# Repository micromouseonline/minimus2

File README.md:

# MINIMUS-2
A half size micromouse design.

## Intent

Create hardware and software for a half-size micromouse robot. The design should be simple and easy to reproduce. It is not necessarily meant to compete at the highest levels. Rather, it should provide a working platform for beginners while still forming the basis for more performant derivatives.

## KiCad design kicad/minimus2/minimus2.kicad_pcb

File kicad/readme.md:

# KiCAD design files for Minimus

All ECAD work is done wih KiCad V8.0

## Libraries

 - Add the JLCPCB parts library by following the instructions here:
    https://github.com/CDFER/JLCPCB-Kicad-Library

    This library contains all the basic parts avaiable from the JLCPCB assembly service, inclluding their footprints and part references.

    As far as I know, the library source is updated every day but the local copy is not so all parts should be checked at the time of a request for manufacture.

    Updates can be done manually from the Plugin manager.

    Since the library is a git repository, it might be possible to clone or fork it, create a local branch and edit the footprints that way.

 - There will also be a custom project library for the parts used in minimus.

## Plugins

 - Add the KiCAD JLC PCB Tools by following the instructions here
     https://github.com/Bouni/kicad-jlcpcb-tools

## Schematic Style

Note that the symbols used by the JLCPCB parts library do not match the symbols that are the default in KiCAD supplied libraries. The most important attributes are all those relating specifically to the JLCPCB part - size, part number, type and so on. If the symbols are a problem, it might be best to copy each part from the JLCPCB library to the project library and edit the symbol there.

## PCB Style

For a half-size mouse, all the components are small and contained in a small PCB. It is not practical to have the component reference and value for all parts. If the boards are to be manufacured by a service, this is not a great problem. A reference diagram showing the part placement from the FAB layers would be helpful for testing and debugging.

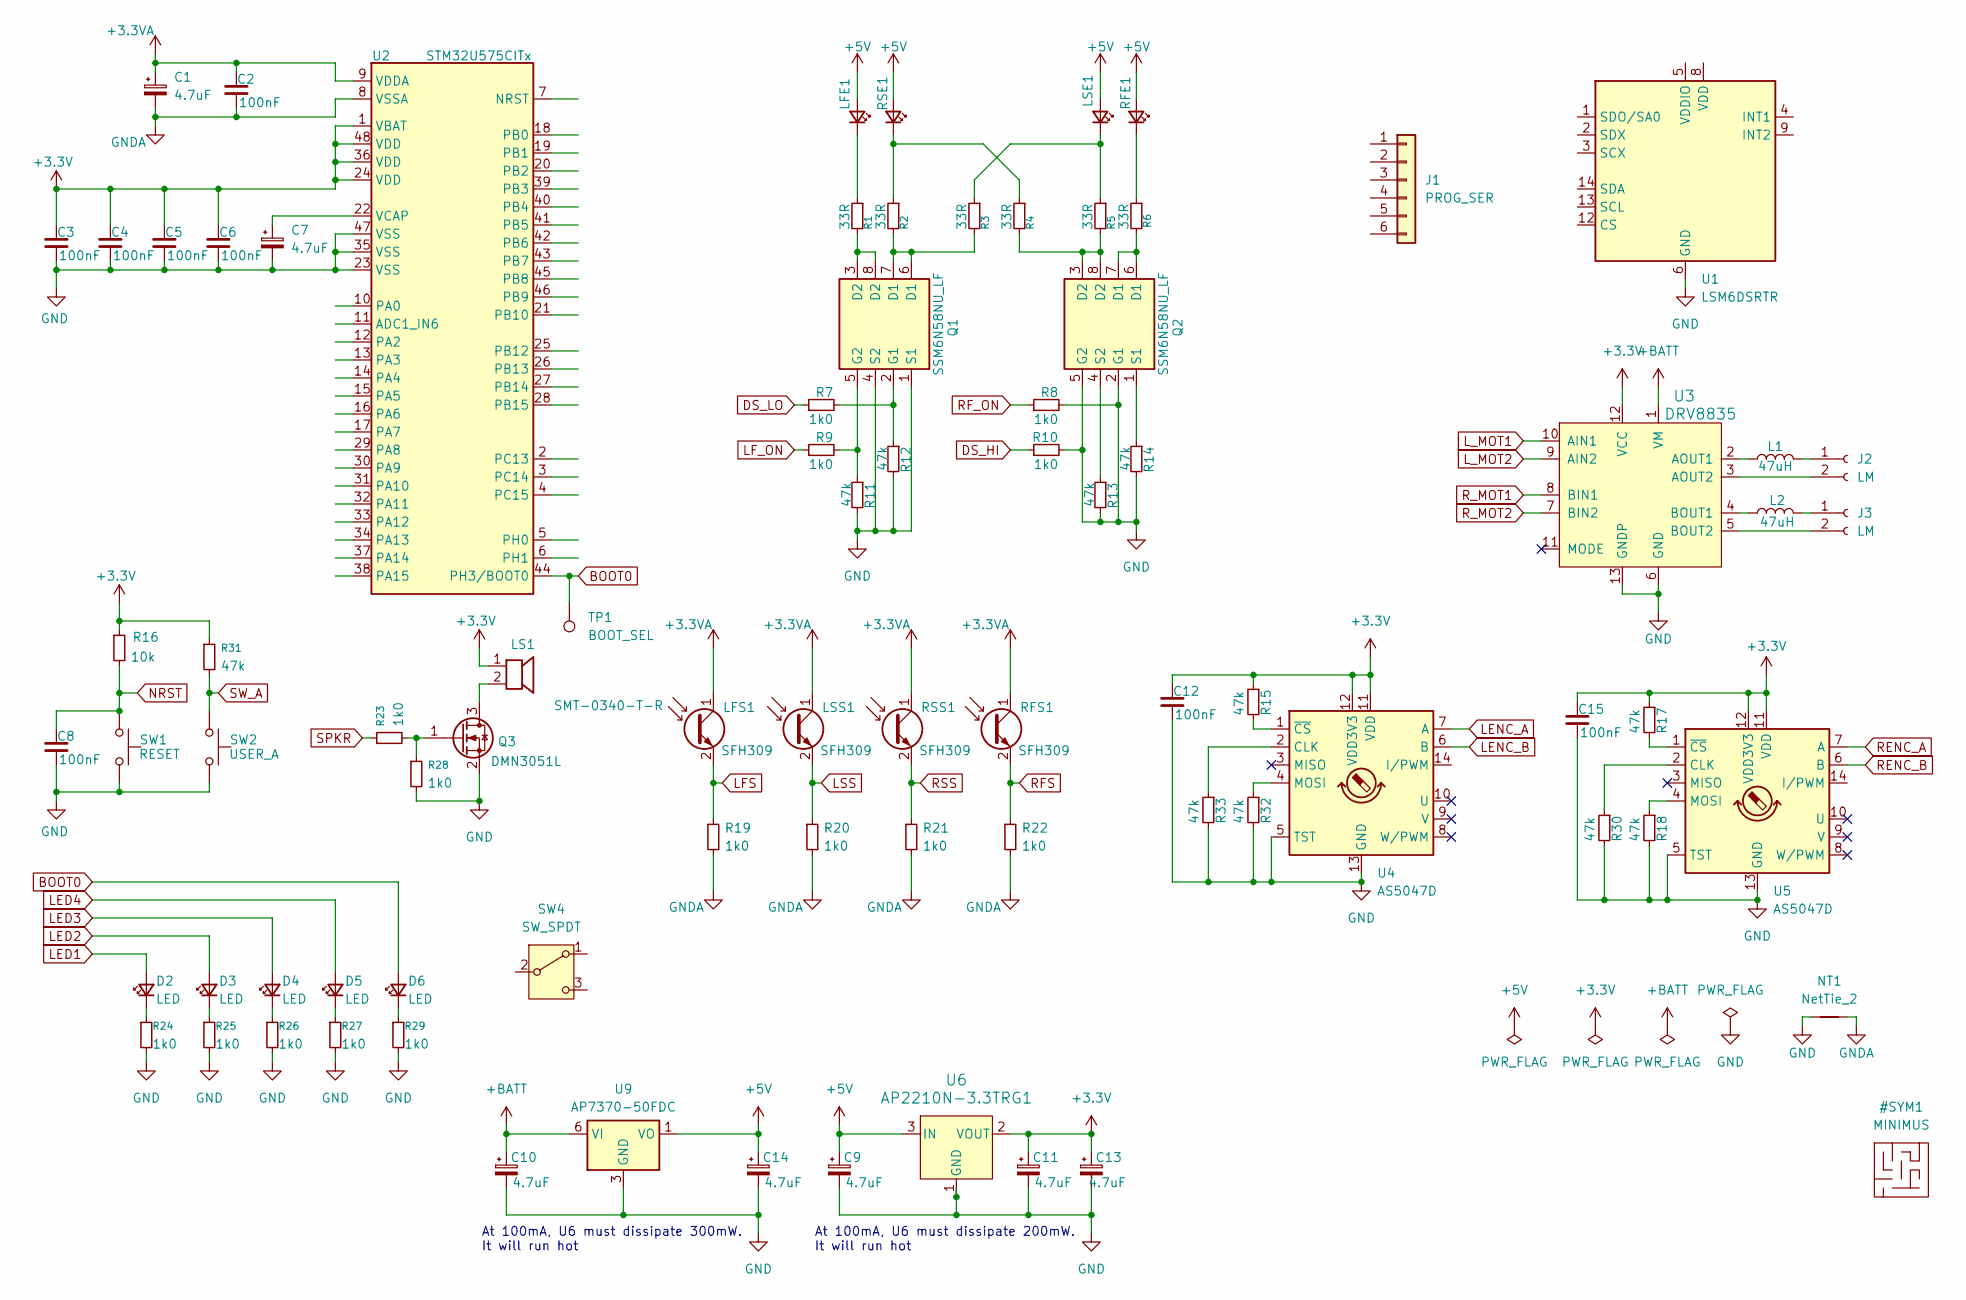
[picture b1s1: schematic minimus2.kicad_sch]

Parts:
C1, C7, C9, C10, C11, C13, C14: 4.7uF; C_0805_2012Metric
C2, C3, C4, C5, C6, C8, C12, C15: 100nF; C_0402_1005Metric
D2, D3, D4, D5, D6: LED; LED_0402_1005Metric
J1: PROG_SER; PinHeader_2x03_P1.27mm_Vertical
J2, J3: LM; PinHeader_1x02_P2.00mm_Vertical
L1, L2: 47uH; IFSC-1515AH-01
LFE1: SFH4050; LED_D3.0mm_Horizontal_O3.81mm_Z6.0mm
LFS1: SFH309; LED_D3.0mm_Horizontal_O1.27mm_Z2.0mm_Clear
LS1: SMT-0340-T-R; LCSC C3811754
LSE1: SFH4050; LED_D3.0mm_Horizontal_O3.81mm_Z6.0mm
LSS1: SFH309; LED_D3.0mm_Horizontal_O1.27mm_Z2.0mm_Clear
NT1: NetTie_2; NetTie-2_SMD_Pad0.5mm
Q1, Q2: SSM6N58NU_LF; SON65P200X200X80-8N; LCSC C262142
Q3: DMN3051L; SOT-23; LCSC C155348
R1, R2, R3, R4, R5, R6: 33R; R_0402_1005Metric
R7, R8, R9, R10, R19, R20, R21, R22, R23, R24, R25, R26, R27, R28, R29: 1k0; R_0402_1005Metric
R11, R12, R13, R14, R15, R17, R18, R30, R31, R32, R33: 47k; R_0402_1005Metric
R16: 10k; R_0402_1005Metric
RFE1: SFH4050; LED_D3.0mm_Horizontal_O3.81mm_Z6.0mm
RFS1: SFH309; LED_D3.0mm_Horizontal_O1.27mm_Z2.0mm_Clear
RSE1: SFH4050; LED_D3.0mm_Horizontal_O3.81mm_Z6.0mm
RSS1: SFH309; LED_D3.0mm_Horizontal_O1.27mm_Z2.0mm_Clear
SW1: RESET; SW_Push_1P1T_NO_CK_KMR2
SW2: USER_A; SW_Push_1P1T_NO_CK_KMR2
SW4: SW_SPDT; CUS-12TB_NDC
TP1: BOOT_SEL; TestPoint_Pad_D1.0mm
U1: LSM6DSRTR; LGA-14_3x2.5mm_P0.5mm_LayoutBorder3x4y; LCSC C784817
U2: STM32U575CITx; LQFP-48_7x7mm_P0.5mm
U3: DRV8835; LCSC C2848981
U4, U5: AS5047D; TSSOP-14_4.4x5mm_P0.65mm
U6: AP2210N-3.3TRG1; AP2210N-x.xTRG1_DIO
U9: AP7370-50FDC; DFN-6-1EP_2x2mm_P0.65mm_EP1.01x1.7mm; LCSC C6125709

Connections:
+3.3V: C3.1, C4.1, C5.1, C6.1, C11.1, C12.1, C13.1, C15.1, LS1.1, R15.1, R16.1, R17.1, R31.1, U2.1 (VBAT), U2.24 (VDD), U2.36 (VDD), U2.48 (VDD), U3.12 (VCC), U4.11 (VDD), U4.12 (VDD3V3), U5.11 (VDD), U5.12 (VDD3V3), U6.2 (VOUT)
+3.3VA: C1.1, C2.1, LFS1.1 (C), LSS1.1 (C), RFS1.1 (C), RSS1.1 (C), U2.9 (VDDA)
+5V: C9.1, C14.1, LFE1.2 (A), LSE1.2 (A), RFE1.2 (A), RSE1.2 (A), U6.3 (IN), U9.1 (VO)
+BATT: C10.1, U3.1 (VM), U9.6 (VI)
BOOT0: D6.2 (A), TP1.1, U2.44 (PH3/BOOT0)
DS_HI: R10.1
DS_LO: R7.1
GND: C3.2, C4.2, C5.2, C6.2, C7.2, C8.2, C9.2, C10.2, C11.2, C12.2, C13.2, C14.2, C15.2, NT1.1, Q1.1 (S1), Q1.4 (S2), Q2.2 (G1), Q2.5 (G2), Q3.2 (S), R8.2, R10.2, R11.2, R12.2, R13.2, R14.2, R18.2, R24.2, R25.2, R26.2, R27.2, R28.2, R29.2, R30.2, R32.2, R33.2, SW1.1, SW2.1, U1.6 (GND), U1.7 (GND), U2.23 (VSS), U2.35 (VSS), U2.47 (VSS), U3.6 (GND), U3.13 (GNDP), U4.5 (TST), U4.13 (GND), U5.5 (TST), U5.13 (GND), U6.1 (GND), U9.3 (GND), U9.7 (GND)
GNDA: C1.2, C2.2, NT1.2, R19.2, R20.2, R21.2, R22.2, U2.8 (VSSA)
LED1: D2.2 (A)
LED2: D3.2 (A)
LED3: D4.2 (A)
LED4: D5.2 (A)
LENC_A: U4.7 (A)
LENC_B: U4.6 (B)
LFS: LFS1.2 (E), R19.1
LF_ON: R9.1
LSS: LSS1.2 (E), R20.1
L_MOT1: U3.10 (AIN1)
L_MOT2: U3.9 (AIN2)
NRST: C8.1, R16.2, SW1.2
unnamed: D2.1 (K), R24.1
unnamed: D3.1 (K), R25.1
unnamed: D4.1 (K), R26.1
unnamed: D5.1 (K), R27.1
unnamed: D6.1 (K), R29.1
unnamed: J2.1, L1.2
unnamed: J2.2, U3.3 (AOUT2)
unnamed: J3.1, L2.2
unnamed: J3.2, U3.5 (BOUT2)
unnamed: LFE1.1 (K), R1.1
unnamed: LSE1.1 (K), R3.1, R5.1
unnamed: Q1.6 (D1), Q1.7 (D1), R2.2, R3.2
unnamed: Q1.3 (D2), Q1.8 (D2), R1.2
unnamed: Q1.2 (G1), R7.2, R12.1
unnamed: Q1.5 (G2), R9.2, R11.1
unnamed: Q2.6 (D1), Q2.7 (D1), R6.2
unnamed: Q2.3 (D2), Q2.8 (D2), R4.2, R5.2
unnamed: Q2.1 (S1), R14.1
unnamed: Q2.4 (S2), R13.1
unnamed: LS1.2, Q3.3 (D)
unnamed: Q3.1 (G), R23.2, R28.1
unnamed: R6.1, RFE1.1 (K)
unnamed: R2.1, R4.1, RSE1.1 (K)
unnamed: C7.1, U2.22 (VCAP)
unnamed: L1.1, U3.2 (AOUT1)
unnamed: L2.1, U3.4 (BOUT1)
unnamed: R33.1, U4.2 (CLK)
unnamed: R32.1, U4.4 (MOSI)
unnamed: R15.2, U4.1 (~CS)
unnamed: R30.1, U5.2 (CLK)
unnamed: R18.1, U5.4 (MOSI)
unnamed: R17.2, U5.1 (~CS)
RENC_A: U5.7 (A)
RENC_B: U5.6 (B)
RFS: R22.1, RFS1.2 (E)
RF_ON: R8.1
RSS: R21.1, RSS1.2 (E)
R_MOT1: U3.8 (BIN1)
R_MOT2: U3.7 (BIN2)
SPKR: R23.1
SW_A: R31.2, SW2.2

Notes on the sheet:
At 100mA, U6 must dissipate 200mW. It will run hot
At 100mA, U6 must dissipate 300mW. It will run hot

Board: 2 copper layers, 82 parts (0 on the bottom side), 45 nets, no tracks yet.

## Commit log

2025-10-21 initial requirements outline
2025-10-21 readme
2025-10-21 clean readme
2025-10-28 add some skeleton kicad files
2025-10-28 add some stm32f413 files
2025-10-30 add some datasheets
2025-10-31 move the datasheets
2025-10-31 add STM32U575/585 docs
2025-10-31 add to kicad project
2025-10-31 add some data files
2025-11-27 add motor mount models
2025-11-27 update the footprints
2025-11-27 update the symbols
2025-11-27 update PCB with motors
2025-11-27 add datasheet for AP7370 LDO regulator
2025-11-27 add footprint for AP7370 regulator
2025-11-27 update power supply
2025-11-27 add a regulator datasheet
2025-11-27 extend the mouse by 5mm to rear
2025-11-29 update the AS5047 symbol
2025-11-29 update EDA
2025-11-29 simplifythe processor pinout table
2025-11-29 add revised thin motor mounts
2025-11-29 update the motor mount footprints
2025-11-29 update the motor mounts
2025-11-29 add guideline graduations to silkscreen
2025-11-29 populate the encoder carriers
2025-11-30 add MA730 library files
2025-12-03 add drivetrain sketch
2025-12-03 update encoder board size
